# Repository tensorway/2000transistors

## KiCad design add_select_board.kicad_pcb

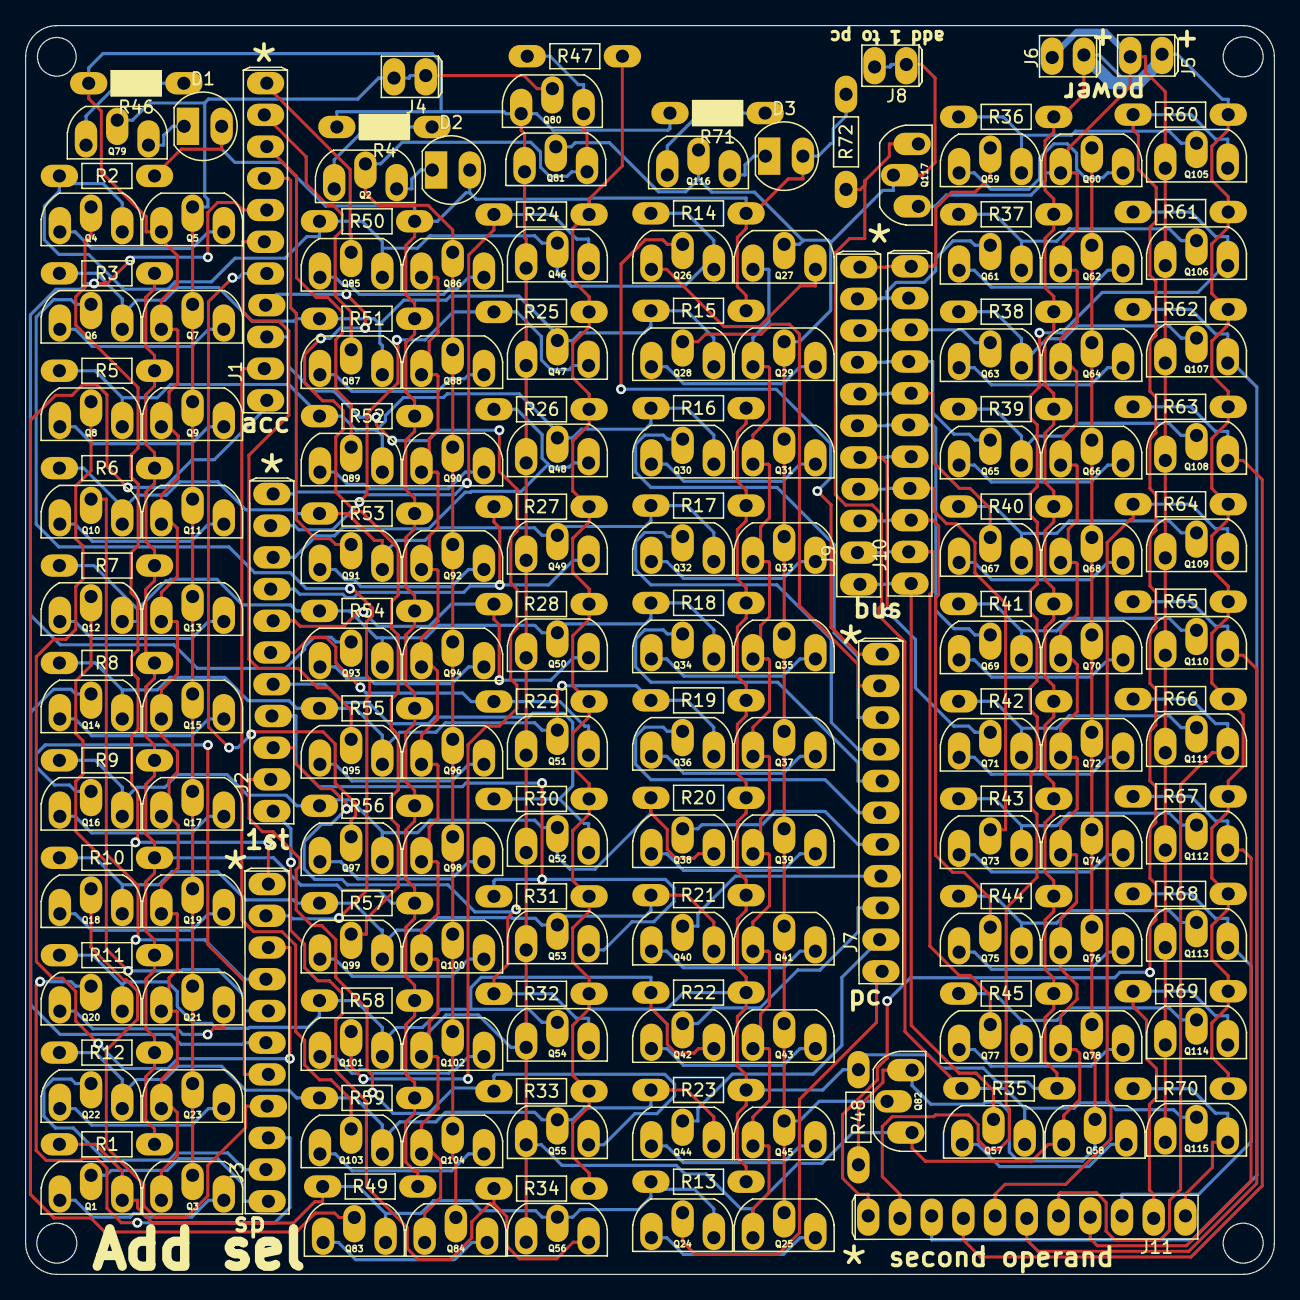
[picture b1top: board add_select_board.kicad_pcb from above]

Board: 2 copper layers, 100.0 x 100.0 mm, 203 parts (0 on the bottom side), 144 nets.

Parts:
D1, D2, D3: LED; led_5mm_tight
J1: acc; 11pin_tight
J2, J10, J11: Conn_01x11_Male; 11pin_tight
J3: sp; 11pin_tight
J4: sp_offset; 2pin_tight
J5, J6: Conn_01x02_Male; 2pin_tight
J7: pc; 11pin_tight
J8: add_1_to_pc; 2pin_tight
J9: bus; 11pin_tight
Q1, Q2, Q3, Q4, Q5, Q6, Q7, Q8, Q9, Q10, Q11, Q12, Q13, Q14, Q15, Q16, Q17, Q18, Q19, Q20, Q21, Q22, Q23, Q24, Q25, Q26, Q27, Q28, Q29, Q30, Q31, Q32, Q33, Q34, Q35, Q36, Q37, Q38, Q39, Q40, Q41, Q42, Q43, Q44, Q45, Q46, Q47, Q48, Q49, Q50, Q51, Q52, Q53, Q54, Q55, Q56, Q57, Q58, Q59, Q60, Q61, Q62, Q63, Q64, Q65, Q66, Q67, Q68, Q69, Q70, Q71, Q72, Q73, Q74, Q75, Q76, Q77, Q78, Q79, Q80, Q81, Q82, Q83, Q84, Q85, Q86, Q87, Q88, Q89, Q90, Q91, Q92, Q93, Q94, Q95, Q96, Q97, Q98, Q99, Q100, Q101, Q102, Q103, Q104, Q105, Q106, Q107, Q108, Q109, Q110, Q111, Q112, Q113, Q114, Q115, Q116, Q117: 2N7000; 2n7000_tight
R1, R2, R3, R5, R6, R7, R8, R9, R10, R11, R12, R13, R14, R15, R16, R17, R18, R19, R20, R21, R22, R23, R24, R25, R26, R27, R28, R29, R30, R31, R32, R33, R34, R35, R36, R37, R38, R39, R40, R41, R42, R43, R44, R45, R47, R48, R49, R50, R51, R52, R53, R54, R55, R56, R57, R58, R59, R60, R61, R62, R63, R64, R65, R66, R67, R68, R69, R70, R72: R; resistor_tight
R4, R46, R71: R; resistor_led_tight

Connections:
+5V: D1.2, D2.2, D3.2, J5.1, J6.1, R1.1, R2.1, R3.1, R5.1, R6.1, R7.1, R8.1, R9.1, R10.1, R11.1, R12.1, R13.1, R14.1, R15.1, R16.1, R17.1, R18.1, R19.1, R20.1, R21.1, R22.1, R23.1, R24.1, R25.1, R26.1, R27.1, R28.1, R29.1, R30.1, R31.1, R32.1, R33.1, R34.1, R35.1, R36.1, R37.1, R38.1, R39.1, R40.1, R41.1, R42.1, R43.1, R44.1, R45.1, R47.1, R48.1, R49.1, R50.1, R51.1, R52.1, R53.1, R54.1, R55.1, R56.1, R57.1, R58.1, R59.1, R60.1, R61.1, R62.1, R63.1, R64.1, R65.1, R66.1, R67.1, R68.1, R69.1, R70.1, R72.1
/Sheet63E190E6/a: Q1.3, Q24.3, Q56.2, Q83.3, R1.2, R13.2, R49.2
/Sheet63E190E6/ain: J1.1, Q83.2
/Sheet63E190E6/b: Q22.3, Q44.3, Q55.2, Q103.3, R12.2, R23.2, R59.2
/Sheet63E190E6/bin: J1.2, Q103.2
/Sheet63E190E6/c: Q20.3, Q42.3, Q54.2, Q101.3, R11.2, R22.2, R58.2
/Sheet63E190E6/cin: J1.3, Q101.2
/Sheet63E190E6/d: Q18.3, Q40.3, Q53.2, Q99.3, R10.2, R21.2, R57.2
/Sheet63E190E6/din: J1.4, Q99.2
/Sheet63E190E6/e: Q16.3, Q38.3, Q52.2, Q97.3, R9.2, R20.2, R56.2
/Sheet63E190E6/ein: J1.5, Q97.2
/Sheet63E190E6/enable: Q2.2, Q80.3, Q81.3, Q84.2, Q86.2, Q88.2, Q90.2, Q92.2, Q94.2, Q96.2, Q98.2, Q100.2, Q102.2, Q104.2, R47.2
/Sheet63E190E6/f: Q14.3, Q36.3, Q51.2, Q95.3, R8.2, R19.2, R55.2
/Sheet63E190E6/fin: J1.6, Q95.2
/Sheet63E190E6/g: Q12.3, Q34.3, Q50.2, Q93.3, R7.2, R18.2, R54.2
/Sheet63E190E6/gin: J1.7, Q93.2
/Sheet63E190E6/h: Q10.3, Q32.3, Q49.2, Q91.3, R6.2, R17.2, R53.2
/Sheet63E190E6/hin: J1.8, Q91.2
/Sheet63E190E6/i: Q8.3, Q30.3, Q48.2, Q89.3, R5.2, R16.2, R52.2
/Sheet63E190E6/iin: J1.9, Q89.2
/Sheet63E190E6/j: Q6.3, Q28.3, Q47.2, Q87.3, R3.2, R15.2, R51.2
/Sheet63E190E6/jin: J1.10, Q87.2
/Sheet63E190E6/k: Q4.3, Q26.3, Q46.2, Q85.3, R2.2, R14.2, R50.2
/Sheet63E190E6/kin: J1.11, Q85.2
/Sheet63F8C225/a: J2.1, Q56.3, R34.2
/Sheet63F8C225/b: J2.2, Q55.3, R33.2
/Sheet63F8C225/c: J2.3, Q54.3, R32.2
/Sheet63F8C225/d: J2.4, Q53.3, R31.2
/Sheet63F8C225/e: J2.5, Q52.3, R30.2
/Sheet63F8C225/f: J2.6, Q51.3, R29.2
/Sheet63F8C225/g: J2.7, Q50.3, R28.2
/Sheet63F8C225/h: J2.8, Q49.3, R27.2
/Sheet63F8C225/i: J2.9, Q48.3, R26.2
/Sheet63F8C225/j: J2.10, Q47.3, R25.2
/Sheet63F8C225/k: J2.11, Q46.3, R24.2
/Sheet6433CCB9/a: J4.1, J4.2, Q3.2, Q5.2, Q7.2, Q9.2, Q11.2, Q13.2, Q15.2, Q17.2, Q19.2, Q21.2, Q23.2, Q79.2, Q80.2
/Sheet6433CCB9/b: J8.1, J8.2, Q25.2, Q27.2, Q29.2, Q31.2, Q33.2, Q35.2, Q37.2, Q39.2, Q41.2, Q43.2, Q45.2, Q81.2, Q82.2, Q116.2, Q117.2
/sheet63E35C38/ain: J7.1, Q24.2
/sheet63E35C38/bin: J7.2, Q44.2
/sheet63E35C38/cin: J7.3, Q42.2
/sheet63E35C38/din: J7.4, Q40.2
/sheet63E35C38/ein: J7.5, Q38.2
/sheet63E35C38/fin: J7.6, Q36.2
/sheet63E35C38/gin: J7.7, Q34.2
/sheet63E35C38/hin: J7.8, Q32.2
/sheet63E35C38/iin: J7.9, Q30.2
/sheet63E35C38/jin: J7.10, Q28.2
/sheet63E35C38/kin: J7.11, Q26.2
/sheet63E3338D/ain: J3.1, Q1.2
/sheet63E3338D/bin: J3.2, Q22.2
/sheet63E3338D/cin: J3.3, Q20.2
/sheet63E3338D/din: J3.4, Q18.2
/sheet63E3338D/ein: J3.5, Q16.2
/sheet63E3338D/fin: J3.6, Q14.2
/sheet63E3338D/gin: J3.7, Q12.2
/sheet63E3338D/hin: J3.8, Q10.2
/sheet63E3338D/iin: J3.9, Q8.2
/sheet63E3338D/jin: J3.10, Q6.2
/sheet63E3338D/kin: J3.11, Q4.2
/sheet63FBA840/a: Q57.3, Q115.2, Q117.3, R35.2, R72.2
/sheet63FBA840/ain: J9.1, J10.1, Q57.2
/sheet63FBA840/b: Q77.3, Q114.2, R45.2
/sheet63FBA840/bin: J9.2, J10.2, Q77.2
/sheet63FBA840/c: Q75.3, Q113.2, R44.2
/sheet63FBA840/cin: J9.3, J10.3, Q75.2
/sheet63FBA840/d: Q73.3, Q112.2, R43.2
/sheet63FBA840/din: J9.4, J10.4, Q73.2
/sheet63FBA840/e: Q71.3, Q111.2, R42.2
/sheet63FBA840/ein: J9.5, J10.5, Q71.2
/sheet63FBA840/enable: Q58.2, Q60.2, Q62.2, Q64.2, Q66.2, Q68.2, Q70.2, Q72.2, Q74.2, Q76.2, Q78.2, Q82.3, R48.2
/sheet63FBA840/f: Q69.3, Q110.2, R41.2
/sheet63FBA840/fin: J9.6, J10.6, Q69.2
/sheet63FBA840/g: Q67.3, Q109.2, R40.2
/sheet63FBA840/gin: J9.7, J10.7, Q67.2
/sheet63FBA840/h: Q65.3, Q108.2, R39.2
/sheet63FBA840/hin: J9.8, J10.8, Q65.2
/sheet63FBA840/i: Q63.3, Q107.2, R38.2
/sheet63FBA840/iin: J9.9, J10.9, Q63.2
/sheet63FBA840/j: Q61.3, Q106.2, R37.2
/sheet63FBA840/jin: J9.10, J10.10, Q61.2
/sheet63FBA840/k: Q59.3, Q105.2, R36.2
/sheet63FBA840/kin: J9.11, J10.11, Q59.2
/sheet63FBA842/a: J11.1, Q115.3, R70.2
/sheet63FBA842/b: J11.2, Q114.3, R69.2
/sheet63FBA842/c: J11.3, Q113.3, R68.2
/sheet63FBA842/d: J11.4, Q112.3, R67.2
/sheet63FBA842/e: J11.5, Q111.3, R66.2
/sheet63FBA842/f: J11.6, Q110.3, R65.2
/sheet63FBA842/g: J11.7, Q109.3, R64.2
/sheet63FBA842/h: J11.8, Q108.3, R63.2
/sheet63FBA842/i: J11.9, Q107.3, R62.2
/sheet63FBA842/j: J11.10, Q106.3, R61.2
/sheet63FBA842/k: J11.11, Q105.3, R60.2
GND: J5.2, J6.2, Q3.1, Q5.1, Q7.1, Q9.1, Q11.1, Q13.1, Q15.1, Q17.1, Q19.1, Q21.1, Q23.1, Q25.1, Q27.1, Q29.1, Q31.1, Q33.1, Q35.1, Q37.1, Q39.1, Q41.1, Q43.1, Q45.1, Q46.1, Q47.1, Q48.1, Q49.1, Q50.1, Q51.1, Q52.1, Q53.1, Q54.1, Q55.1, Q56.1, Q58.1, Q60.1, Q62.1, Q64.1, Q66.1, Q68.1, Q70.1, Q72.1, Q74.1, Q76.1, Q78.1, Q80.1, Q81.1, Q82.1, Q84.1, Q86.1, Q88.1, Q90.1, Q92.1, Q94.1, Q96.1, Q98.1, Q100.1, Q102.1, Q104.1, Q105.1, Q106.1, Q107.1, Q108.1, Q109.1, Q110.1, Q111.1, Q112.1, Q113.1, Q114.1, Q115.1, Q117.1, R4.2, R46.2, R71.2
unnamed: D1.1, Q79.3
unnamed: D2.1, Q2.3
unnamed: D3.1, Q116.3
unnamed: Q1.1, Q3.3
unnamed: Q2.1, R4.1
unnamed: Q4.1, Q5.3
unnamed: Q6.1, Q7.3
unnamed: Q8.1, Q9.3
unnamed: Q10.1, Q11.3
unnamed: Q12.1, Q13.3
unnamed: Q14.1, Q15.3
unnamed: Q16.1, Q17.3
unnamed: Q18.1, Q19.3
unnamed: Q20.1, Q21.3
unnamed: Q22.1, Q23.3
unnamed: Q24.1, Q25.3
unnamed: Q26.1, Q27.3
unnamed: Q28.1, Q29.3
unnamed: Q30.1, Q31.3
unnamed: Q32.1, Q33.3
unnamed: Q34.1, Q35.3
unnamed: Q36.1, Q37.3
unnamed: Q38.1, Q39.3
unnamed: Q40.1, Q41.3
unnamed: Q42.1, Q43.3
unnamed: Q44.1, Q45.3
unnamed: Q57.1, Q58.3
unnamed: Q59.1, Q60.3
unnamed: Q61.1, Q62.3
unnamed: Q63.1, Q64.3
unnamed: Q65.1, Q66.3
unnamed: Q67.1, Q68.3
unnamed: Q69.1, Q70.3
unnamed: Q71.1, Q72.3
unnamed: Q73.1, Q74.3
unnamed: Q75.1, Q76.3
unnamed: Q77.1, Q78.3
unnamed: Q79.1, R46.1
unnamed: Q83.1, Q84.3
unnamed: Q85.1, Q86.3
unnamed: Q87.1, Q88.3
unnamed: Q89.1, Q90.3
unnamed: Q91.1, Q92.3
unnamed: Q93.1, Q94.3
unnamed: Q95.1, Q96.3
unnamed: Q97.1, Q98.3
unnamed: Q99.1, Q100.3
unnamed: Q101.1, Q102.3
unnamed: Q103.1, Q104.3
unnamed: Q116.1, R71.1
